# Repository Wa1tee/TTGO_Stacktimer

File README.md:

# TTGO_Stacktimer

A Stackmat style timer utilizing a TTGO T-Display ESP32 development board and Cherry MX style mechanical keyboard switches with 6.25u spacebars as buttons.

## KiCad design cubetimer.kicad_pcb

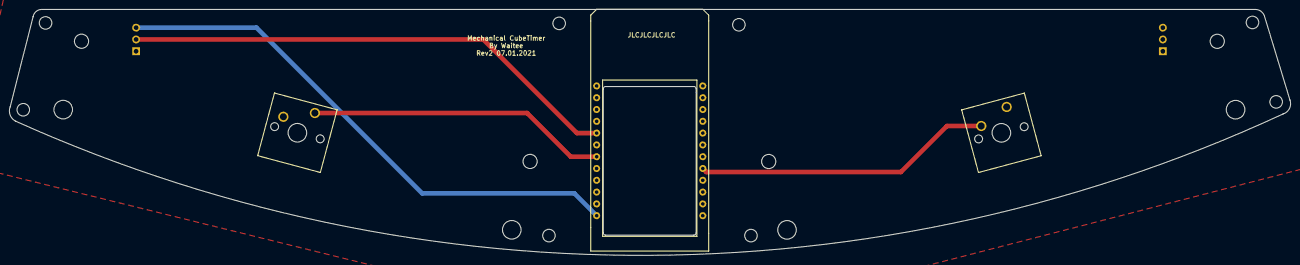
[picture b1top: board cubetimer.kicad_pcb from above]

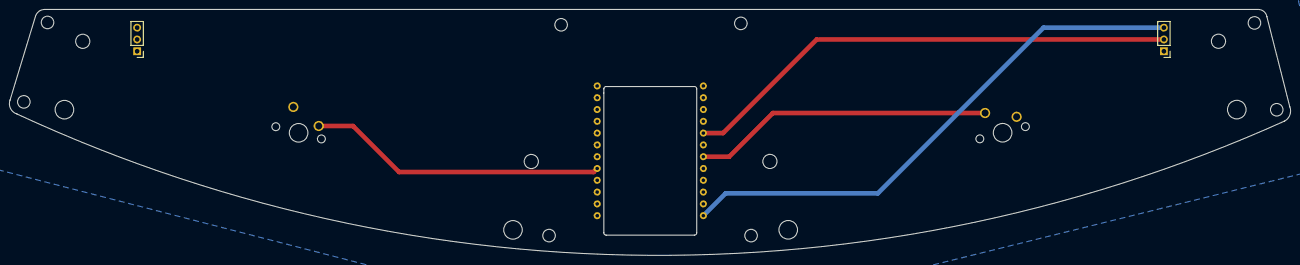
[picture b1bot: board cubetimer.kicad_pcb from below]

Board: 2 copper layers, 275.9 x 53.0 mm, 13 parts (2 on the bottom side), 5 nets.

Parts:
H1, H2, H3, H4, H5, H6, H7, H8: MountingHole; MountingHole_2.7mm_M2.5_DIN965
J1, J2: Conn_01x03_Male; PinHeader_1x03_P2.54mm_Vertical
SW1, SW2: SW_Push; SW_Cherry_MX_6.25u_PCB
U1: TTGO_T-Display_ESP32; TTGO_ESP32_TDisplay_v1.1

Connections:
+3V3: J1.3, U1.12, U1.24
Din: J1.2, U1.5
GND: J1.1, SW1.2, SW2.1, U1.2, U1.13, U1.14, U1.22, U1.23
unnamed: SW1.1, U1.7
unnamed: SW2.2, U1.17

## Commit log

2021-01-07 Initial commit rev2
2021-01-07 Added 3D render of the timer
